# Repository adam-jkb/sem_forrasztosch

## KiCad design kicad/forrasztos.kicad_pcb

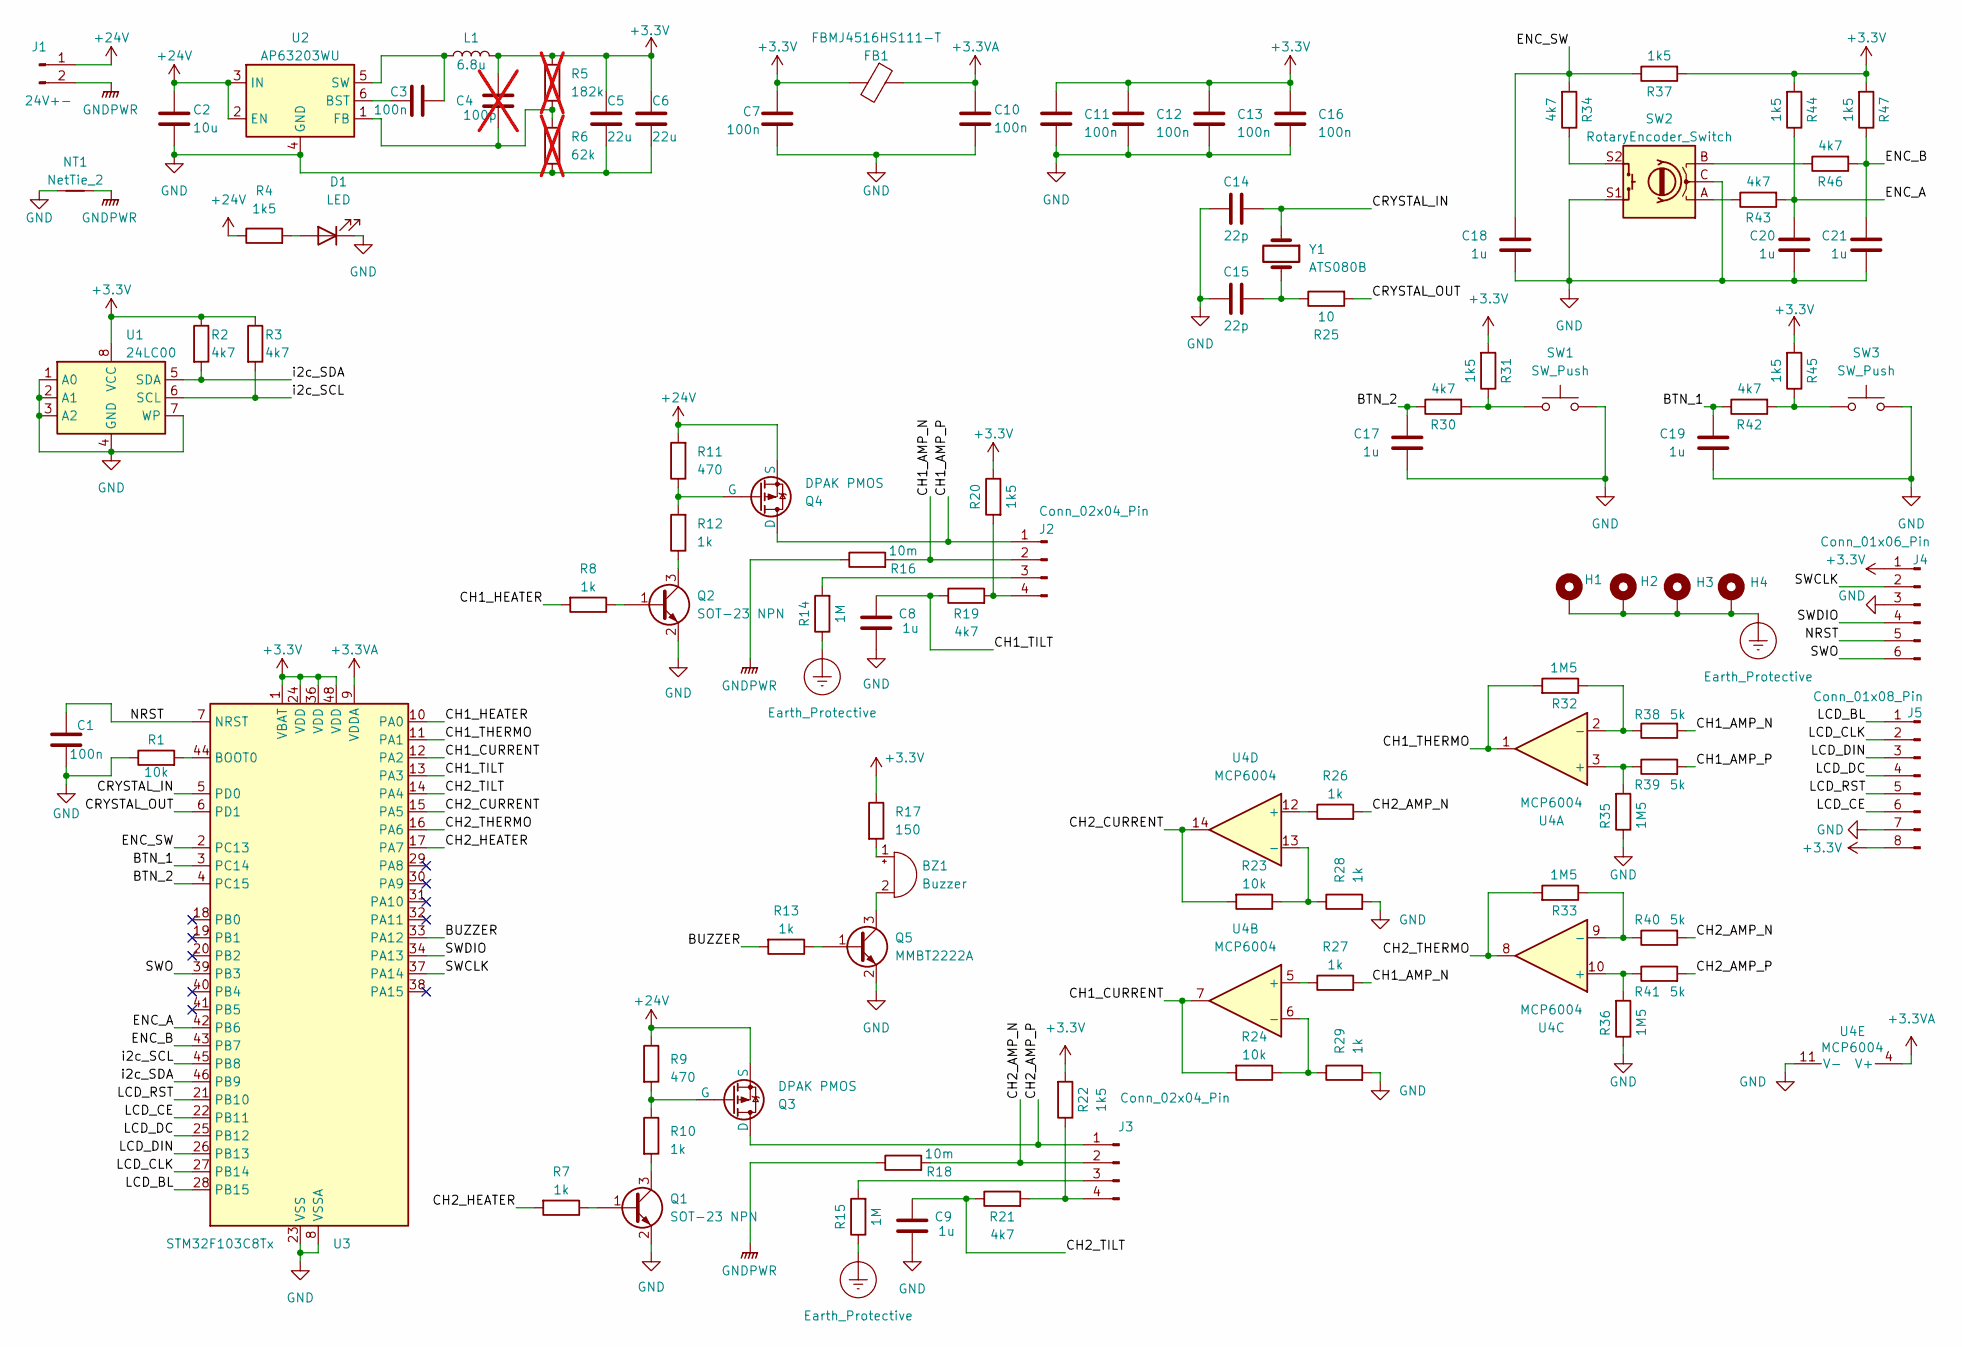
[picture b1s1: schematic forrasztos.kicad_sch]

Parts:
BZ1: Buzzer; BuzzerR9F5
C1, C3, C7, C10, C11, C12, C13, C16: 100n; C_0805_2012Metric_Pad1.18x1.45mm_HandSolder
C2: 10u; C_1206_3216Metric_Pad1.33x1.80mm_HandSolder
C4: 100p; C_0805_2012Metric_Pad1.18x1.45mm_HandSolder; not fitted
C5, C6: 22u; C_1206_3216Metric_Pad1.33x1.80mm_HandSolder
C8, C9, C17, C18, C19, C20, C21: 1u; C_0805_2012Metric_Pad1.18x1.45mm_HandSolder
C14, C15: 22p; C_0805_2012Metric_Pad1.18x1.45mm_HandSolder
D1: LED; LED_D3.0mm
FB1: FBMJ4516HS111-T; Ferrite_0805_2012Metric
H1, H2, H3, H4: MountingHole_Pad; MountingHole_2.7mm_M2.5_DIN965_Pad_TopBottom
J1: 24V+-; CONN-TH_2P-P5.00_L7.6-W10.0
J2, J3: Conn_02x04_Pin; PinHeader_2x04_P2.54mm_Vertical
J4: Conn_01x06_Pin; PinHeader_1x06_P2.54mm_Vertical
J5: Conn_01x08_Pin; PinHeader_1x08_P2.54mm_Vertical
L1: 6.8u; L_TracoPower_TCK-047_5.2x5.8mm
NT1: NetTie_2; NetTie-2_SMD_Pad2.0mm
Q1, Q2: SOT-23 NPN; SOT-323_SC-70_Handsoldering
Q3, Q4: DPAK PMOS; TO-252-2-custom
Q5: MMBT2222A; SOT-323_SC-70_Handsoldering
R1, R23, R24: 10k; R_0805_2012Metric_Pad1.20x1.40mm_HandSolder
R2, R3, R19, R21, R30, R34, R42, R43, R46: 4k7; R_0805_2012Metric_Pad1.20x1.40mm_HandSolder
R4, R20, R22, R31, R37, R44, R45, R47: 1k5; R_0805_2012Metric_Pad1.20x1.40mm_HandSolder
R5: 182k; R_0805_2012Metric_Pad1.20x1.40mm_HandSolder; not fitted
R6: 62k; R_0805_2012Metric_Pad1.20x1.40mm_HandSolder; not fitted
R7, R8, R10, R12, R13, R26, R27, R28, R29: 1k; R_0805_2012Metric_Pad1.20x1.40mm_HandSolder
R9, R11: 470; R_0805_2012Metric_Pad1.20x1.40mm_HandSolder
R14, R15: 1M; R_Axial_DIN0414_L11.9mm_D4.5mm_P15.24mm_Horizontal
R16, R18: 10m; R_1206_3216Metric_Pad1.30x1.75mm_HandSolder
R17: 150; R_0805_2012Metric_Pad1.20x1.40mm_HandSolder
R25: 10; R_0805_2012Metric_Pad1.20x1.40mm_HandSolder
R32, R33, R35, R36: 1M5; R_0805_2012Metric_Pad1.20x1.40mm_HandSolder
R38, R39, R40, R41: 5k; R_0805_2012Metric_Pad1.20x1.40mm_HandSolder
SW1, SW3: SW_Push; SW_PUSH-12mm
SW2: RotaryEncoder_Switch; RotaryEncoder_Alps_EC12E-Switch_Vertical_H20mm
U1: 24LC00; DIP-8_W7.62mm
U2: AP63203WU; TSOT-23-6
U3: STM32F103C8Tx; LQFP-48_7x7mm_P0.5mm
U4: MCP6004; SOIC-14_3.9x8.7mm_P1.27mm
Y1: ATS080B; Crystal_HC49-U_Vertical

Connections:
+3.3V: C4.1, C5.1, C6.1, C7.1, C11.1, C12.1, C13.1, C16.1, FB1.2, J4.1, J5.8, L1.2, R2.1, R3.1, R5.1, R17.1, R20.1, R22.2, R31.2, R37.2, R44.2, R45.2, R47.2, U1.8 (VCC), U3.1 (VBAT), U3.24 (VDD), U3.36 (VDD), U3.48 (VDD)
+3.3VA: C10.1, FB1.1, U3.9 (VDDA), U4.4 (V+)
+24V: C2.1, J1.1, Q3.3 (S), Q4.3 (S), R4.1, R9.1, R11.2, U2.2 (EN), U2.3 (IN)
/BTN_1: C19.1, R42.1, U3.3 (PC14)
/BTN_2: C17.1, R30.1, U3.4 (PC15)
/BUZZER: R13.2, U3.33 (PA12)
/CH1_AMP_N: J2.2, R16.2, R27.2, R38.2
/CH1_AMP_P: J2.1, Q4.1 (D), R39.2
/CH1_CURRENT: R24.2, U3.12 (PA2), U4.7
/CH1_HEATER: R8.2, U3.10 (PA0)
/CH1_THERMO: R32.2, U3.11 (PA1), U4.1
/CH1_TILT: C8.2, R19.1, U3.13 (PA3)
/CH2_AMP_N: J3.2, R18.2, R26.2, R40.2
/CH2_AMP_P: J3.1, Q3.1 (D), R41.2
/CH2_CURRENT: R23.2, U3.15 (PA5), U4.14
/CH2_HEATER: R7.2, U3.17 (PA7)
/CH2_THERMO: R33.2, U3.16 (PA6), U4.8
/CH2_TILT: C9.2, R21.1, U3.14 (PA4)
/CRYSTAL_IN: C14.2, U3.5 (PD0), Y1.1
/CRYSTAL_OUT: R25.2, U3.6 (PD1)
/ENC_A: C20.1, R43.2, R44.1, U3.42 (PB6)
/ENC_B: C21.1, R46.2, R47.1, U3.43 (PB7)
/ENC_SW: C18.1, R34.2, R37.1, U3.2 (PC13)
/LCD_BL: J5.1, U3.28 (PB15)
/LCD_CE: J5.6, U3.22 (PB11)
/LCD_CLK: J5.2, U3.27 (PB14)
/LCD_DC: J5.4, U3.25 (PB12)
/LCD_DIN: J5.3, U3.26 (PB13)
/LCD_RST: J5.5, U3.21 (PB10)
/NRST: C1.2, J4.5, U3.7 (NRST)
/SWCLK: J4.2, U3.37 (PA14)
/SWDIO: J4.4, U3.34 (PA13)
/SWO: J4.6, U3.39 (PB3)
/i2c_SCL: R3.2, U1.6 (SCL), U3.45 (PB8)
/i2c_SDA: R2.2, U1.5 (SDA), U3.46 (PB9)
Earth_Protective: H1.1, H2.1, H3.1, H4.1, R14.1, R15.1
GND: C1.1, C2.2, C5.2, C6.2, C7.2, C8.1, C9.1, C10.2, C11.2, C12.2, C13.2, C14.1, C15.1, C16.2, C17.2, C18.2, C19.2, C20.2, C21.2, D1.1 (K), J4.3, J5.7, NT1.1, Q1.2 (E), Q2.2 (E), Q5.2 (E), R1.1, R6.2, R28.2, R29.2, R35.1, R36.1, SW1.2, SW2.C, SW2.S1, SW3.2, U1.1 (A0), U1.2 (A1), U1.3 (A2), U1.4 (GND), U1.7 (WP), U2.4 (GND), U3.8 (VSSA), U3.23 (VSS), U3.35 (VSS), U3.47 (VSS), U4.11 (V-)
GNDPWR: J1.2, NT1.2, R16.1, R18.1
unnamed: BZ1.1 (+), R17.2
unnamed: BZ1.2 (-), Q5.3 (C)
unnamed: C15.2, R25.1, Y1.2
unnamed: D1.2 (A), R4.2
unnamed: J2.3, R14.2
unnamed: J2.4, R19.2, R20.2
unnamed: J3.3, R15.2
unnamed: J3.4, R21.2, R22.1
unnamed: Q1.1 (B), R7.1
unnamed: Q1.3 (C), R10.2
unnamed: Q2.1 (B), R8.1
unnamed: Q2.3 (C), R12.1
unnamed: Q3.2 (G), R9.2, R10.1
unnamed: Q4.2 (G), R11.1, R12.2
unnamed: Q5.1 (B), R13.1
unnamed: R30.2, R31.1, SW1.1
unnamed: R34.1, SW2.S2
unnamed: R42.2, R45.1, SW3.1
unnamed: R43.1, SW2.A
unnamed: R46.1, SW2.B
unnamed: C3.1, U2.6 (BST)
unnamed: C4.2, R5.2, R6.1, U2.1 (FB)
unnamed: C3.2, L1.1, U2.5 (SW)
unnamed: R1.2, U3.44 (BOOT0)
unnamed: R35.2, R39.1, U4.3 (+)
unnamed: R32.1, R38.1, U4.2 (-)
unnamed: R27.1, U4.5 (+)
unnamed: R24.1, R29.1, U4.6 (-)
unnamed: R36.2, R41.1, U4.10 (+)
unnamed: R33.1, R40.1, U4.9 (-)
unnamed: R26.1, U4.12 (+)
unnamed: R23.1, R28.1, U4.13 (-)

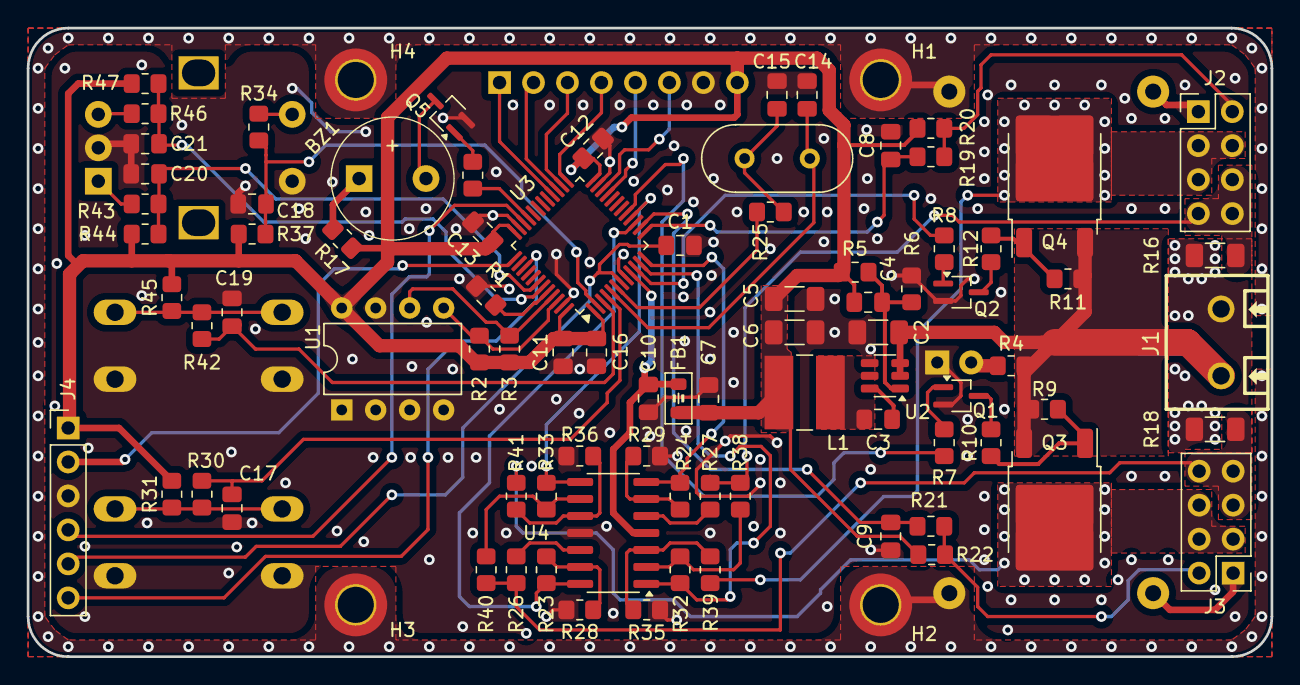
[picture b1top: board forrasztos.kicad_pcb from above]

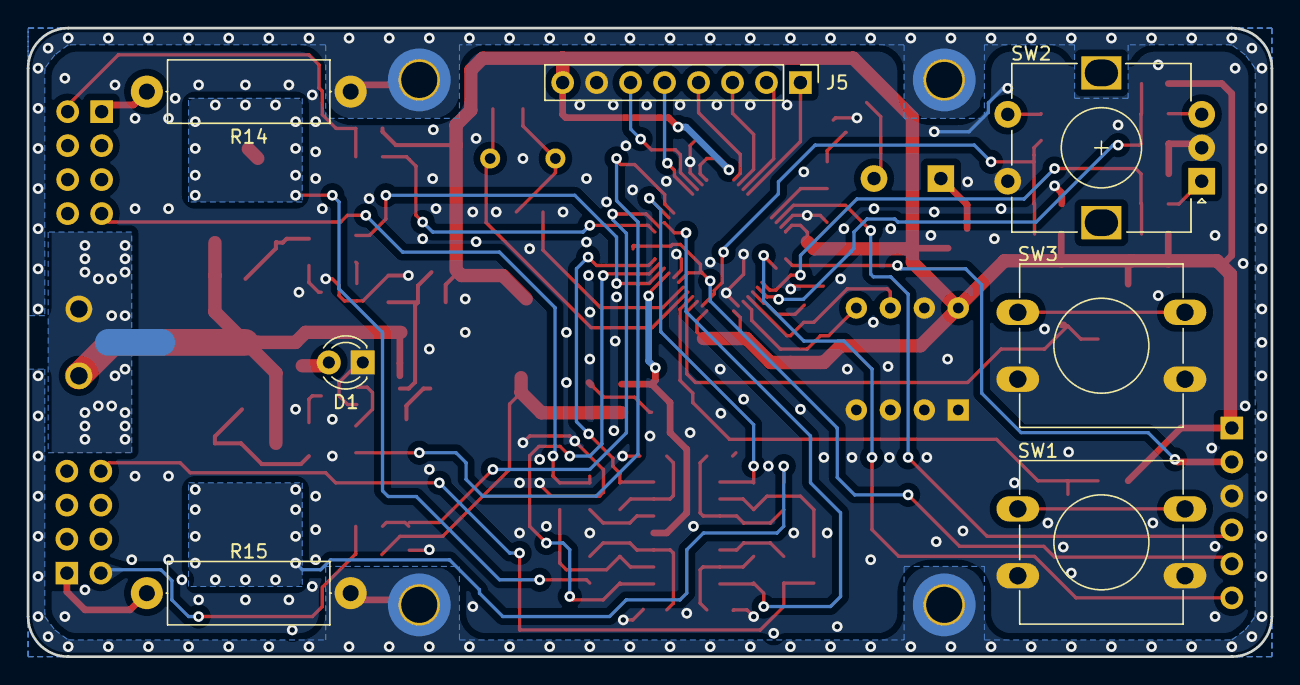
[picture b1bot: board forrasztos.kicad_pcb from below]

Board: 2 copper layers, 93.0 x 47.0 mm, 95 parts (8 on the bottom side), 70 nets.

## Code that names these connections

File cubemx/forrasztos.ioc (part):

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Mcu.Name=STM32F103C(8-B)Tx
Mcu.Package=LQFP48
Mcu.UserName=STM32F103C8Tx
PA0-WKUP.GPIOParameters=GPIO_Label
PA0-WKUP.GPIO_Label=CH1_HEATER
PA0-WKUP.Signal=S_TIM2_CH1_ETR
PA1.GPIOParameters=GPIO_Label
PA1.GPIO_Label=CH1_THERMO
PA1.Signal=ADCx_IN1
PA13.Mode=Trace_Asynchronous_SW
PA13.Signal=SYS_JTMS-SWDIO
PA14.Mode=Trace_Asynchronous_SW
PA14.Signal=SYS_JTCK-SWCLK
PA2.GPIOParameters=GPIO_Label
PA2.GPIO_Label=CH1_CURRENT
PA2.Signal=ADCx_IN2
PA3.GPIOParameters=GPIO_Label
PA3.GPIO_Label=CH1_TILT
PA3.Signal=GPIO_Input
PA4.GPIOParameters=GPIO_Label
PA4.GPIO_Label=CH2_TILT
PA4.Signal=GPIO_Input
PA5.GPIOParameters=GPIO_Label
PA5.GPIO_Label=CH2_CURRENT
PA5.Signal=ADCx_IN5
PA6.GPIOParameters=GPIO_Label
PA6.GPIO_Label=CH2_THERMO
PA6.Signal=S_TIM3_CH1
PA7.GPIOParameters=GPIO_Label
PA7.GPIO_Label=CH2_HEATER
PA7.Signal=S_TIM3_CH2
PB10.GPIOParameters=GPIO_Label
PB10.GPIO_Label=LCD_RST
PB10.Signal=GPIO_Output
PB11.GPIOParameters=GPIO_Label
PB11.GPIO_Label=LCD_CE
PB11.Signal=GPIO_Output
PB12.GPIOParameters=GPIO_Label
PB12.GPIO_Label=LCD_DC
PB12.Signal=GPIO_Output
PB13.GPIOParameters=GPIO_Label
PB13.GPIO_Label=LCD_DIN
PB13.Signal=GPIO_Output
PB14.GPIOParameters=GPIO_Label
PB14.GPIO_Label=LCD_CLK
PB14.Mode=PWM Generation2 CH2N
PB14.Signal=TIM1_CH2N
PB15.GPIOParameters=GPIO_Label
PB15.GPIO_Label=LCD_BL
PB15.Signal=GPIO_Output
PB3.Mode=Trace_Asynchronous_SW
PB3.Signal=SYS_JTDO-TRACESWO
PB6.GPIOParameters=GPIO_Label
PB6.GPIO_Label=ENC_A
PB6.Signal=S_TIM4_CH1
PB7.GPIOParameters=GPIO_Label
PB7.GPIO_Label=ENC_B
PB7.Signal=S_TIM4_CH2
PB8.Mode=I2C
PB8.Signal=I2C1_SCL
PB9.Mode=I2C
PB9.Signal=I2C1_SDA
PC13-TAMPER-RTC.GPIOParameters=GPIO_Label
PC13-TAMPER-RTC.GPIO_Label=ENC_SW
PC13-TAMPER-RTC.Signal=GPIO_Input
PC14-OSC32_IN.GPIOParameters=GPIO_Label
PC14-OSC32_IN.GPIO_Label=BTN_1
PC14-OSC32_IN.Signal=GPXTI14
PC15-OSC32_OUT.GPIOParameters=GPIO_Label
PC15-OSC32_OUT.GPIO_Label=BTN_2
PC15-OSC32_OUT.Signal=GPXTI15
PD0-OSC_IN.Mode=HSE-External-Oscillator
PD0-OSC_IN.Signal=RCC_OSC_IN
PD1-OSC_OUT.Mode=HSE-External-Oscillator
PD1-OSC_OUT.Signal=RCC_OSC_OUT
RCC.SYSCLKFreq_VALUE=48000000
RCC.SYSCLKSource=RCC_SYSCLKSOURCE_PLLCLK
board=custom

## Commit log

2023-04-28 initial
2023-04-29 work on schematic
2023-04-29 sch kb kesz, meg kell egy kis atdolgozas
2023-04-30 added cubemx project and .gitignore
2023-05-01 added csájníz erősítő
2023-05-01 replaced analog logic
2023-05-09 schematic mostly done
2023-07-04 added 2nd channel
2023-07-11 pcb work
2023-07-18 redone pcb
2023-07-25 fixed footprints, power part done
2023-08-14 finished work on pcb
2023-08-14 revA prototype
2023-10-15 cleanup after revision A
2023-11-04 start port of PTDreamer repo
2024-05-09 hw revision
2024-05-13 flip led
2024-05-14 move around some lines
